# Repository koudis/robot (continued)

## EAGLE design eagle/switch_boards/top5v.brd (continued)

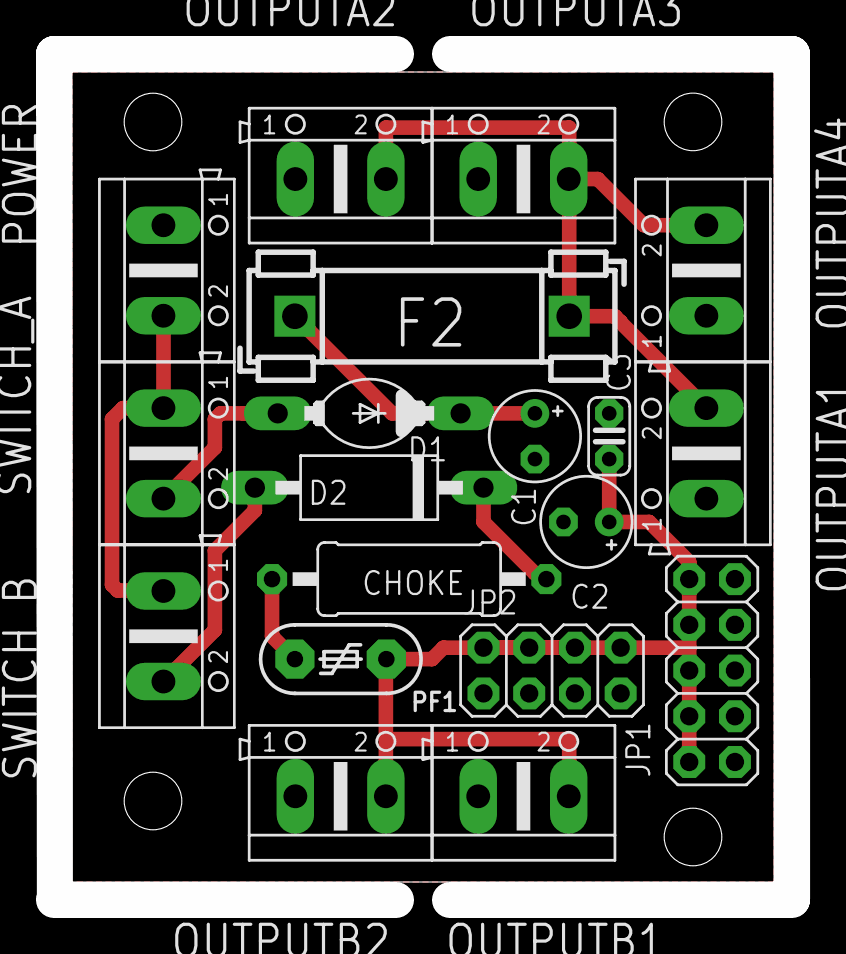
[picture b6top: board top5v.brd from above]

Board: 2 copper layers, 41.0 x 47.0 mm, 19 parts (0 on the bottom side), 9 nets.

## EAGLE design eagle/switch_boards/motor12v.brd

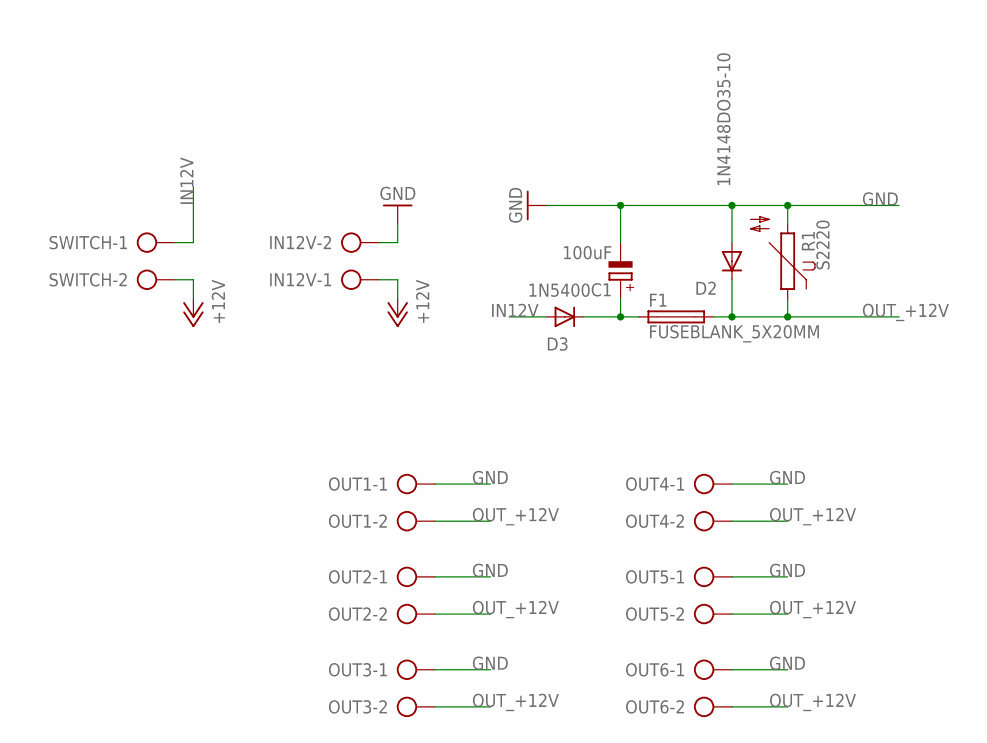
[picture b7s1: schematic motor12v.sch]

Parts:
C1: 100uF; E3,5-8
D2: 1N4148DO35-10; DO35-10
D3: 1N5400; DO201-15
F1: FUSEBLANK_5X20MM; FUSE_HOLDER_5X20MM
IN12V: AK500/2
OUT1, OUT2, OUT3, OUT4, OUT5, OUT6: AK500/2
R1: S2220
SWITCH: AK500/2

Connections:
+12V: IN12V.1, SWITCH.2
EN21: C1.+, D3.C, F1.1
GND: C1.-, D2.A, IN12V.2, OUT1.1, OUT2.1, OUT3.1, OUT4.1, OUT5.1, OUT6.1, R1.2
IN12V: D3.A, SWITCH.1
OUT_+12V: D2.C, F1.2, OUT1.2, OUT2.2, OUT3.2, OUT4.2, OUT5.2, OUT6.2, R1.1

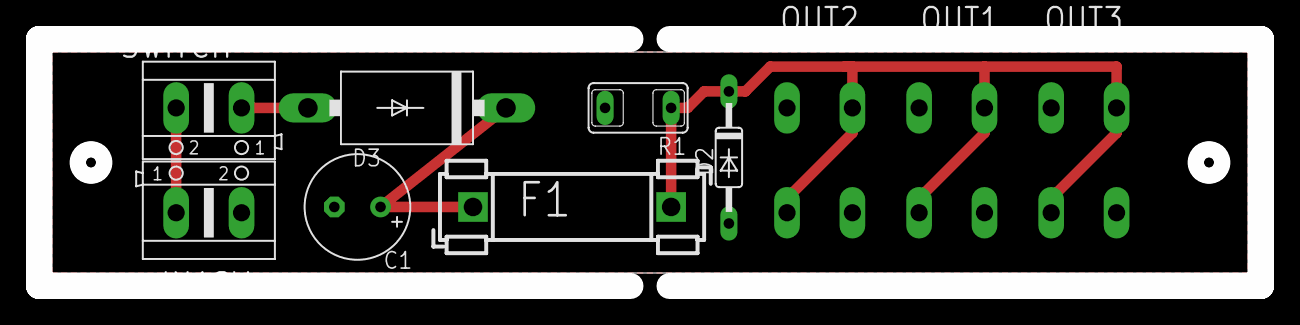
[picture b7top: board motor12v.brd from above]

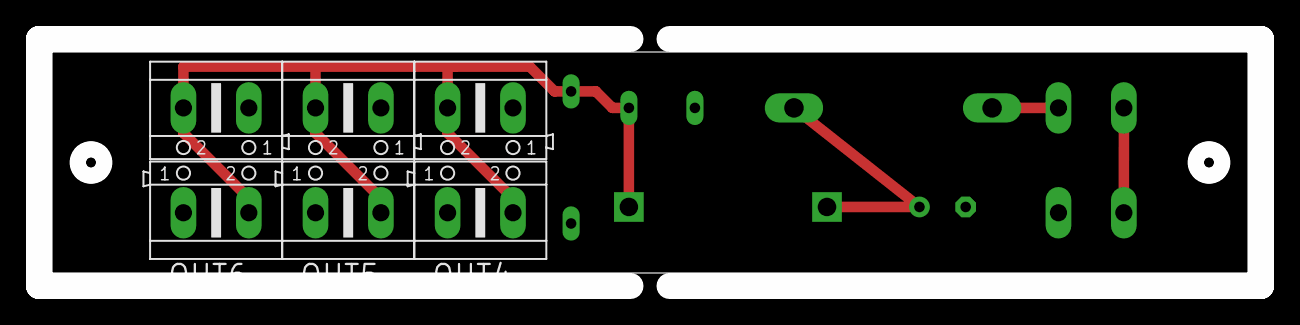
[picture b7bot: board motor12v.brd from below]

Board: 2 copper layers, 94.0 x 19.0 mm, 13 parts (6 on the bottom side), 5 nets.

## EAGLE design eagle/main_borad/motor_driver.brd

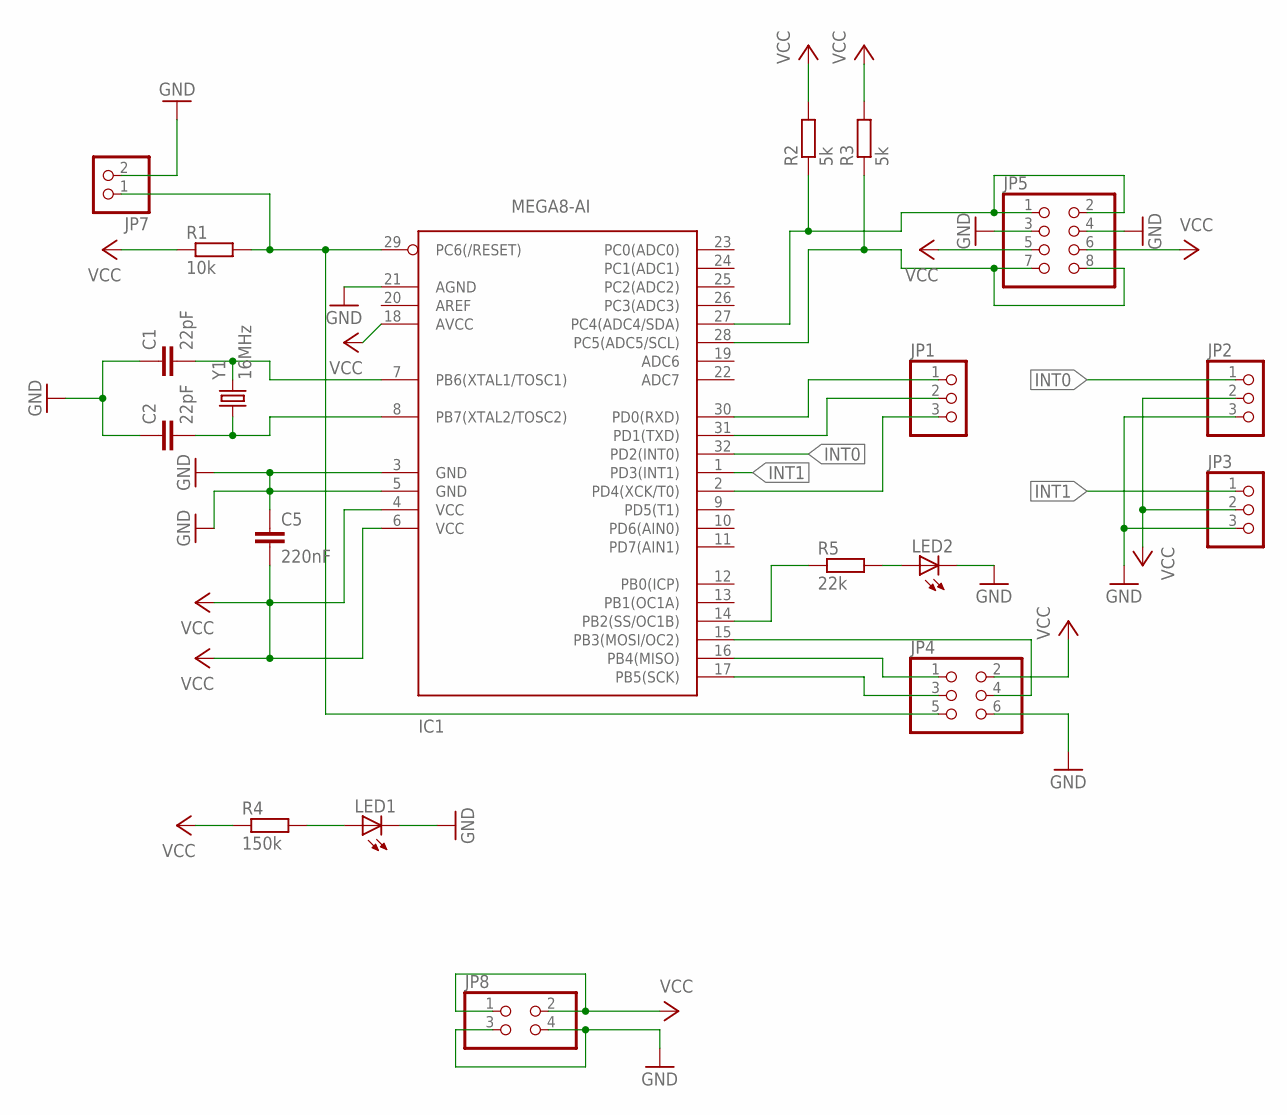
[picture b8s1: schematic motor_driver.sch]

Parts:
C1, C2: 22pF; 1206
C5: 220nF; 0805
IC1: MEGA8-AI; TQFP32-08
JP1, JP2, JP3: PINHD-1X3; 1X03
JP4: PINHD-2X3; 2X03
JP5: PINHD-2X4; 2X04
JP7: PINHD-1X2; 1X02
JP8: PINHD-2X2; 2X02
LED1, LED2: LEDCHIPLED_0805; CHIPLED_0805
R1: 10k; R1206
R2, R3: 5k; R1206
R4: 150k; R0805
R5: 22k; R0805
Y1: 16MHz; HC49UP

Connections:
GND: C1.1, C2.1, C5.1, IC1.3 (GND), IC1.5 (GND), IC1.21 (AGND), JP2.3, JP3.3, JP4.6, JP5.3, JP5.4, JP7.2, JP8.3, JP8.4, LED1.C, LED2.C
INT0: IC1.32 (PD2(INT0)), JP2.1
INT1: IC1.1 (PD3(INT1)), JP3.1
unnamed: IC1.31 (PD1(TXD)), JP1.2
unnamed: C2.2, IC1.8 (PB7(XTAL2/TOSC2)), Y1.1
unnamed: C1.2, IC1.7 (PB6(XTAL1/TOSC1)), Y1.2
unnamed: IC1.14 (PB2(SS/OC1B)), R5.1
unnamed: IC1.30 (PD0(RXD)), JP1.1
unnamed: IC1.2 (PD4(XCK/T0)), JP1.3
unnamed: IC1.15 (PB3(MOSI/OC2)), JP4.4
unnamed: IC1.28 (PC5(ADC5/SCL)), JP5.7, JP5.8, R3.1
unnamed: IC1.27 (PC4(ADC4/SDA)), JP5.1, JP5.2, R2.1
unnamed: LED1.A, R4.2
unnamed: IC1.17 (PB5(SCK)), JP4.3
unnamed: IC1.16 (PB4(MISO)), JP4.1
unnamed: LED2.A, R5.2
RESET: IC1.29 (PC6(/RESET)), JP4.5, JP7.1, R1.2
VCC: C5.2, IC1.4 (VCC), IC1.6 (VCC), IC1.18 (AVCC), JP2.2, JP3.2, JP4.2, JP5.5, JP5.6, JP8.1, JP8.2, R1.1, R2.2, R3.2, R4.1

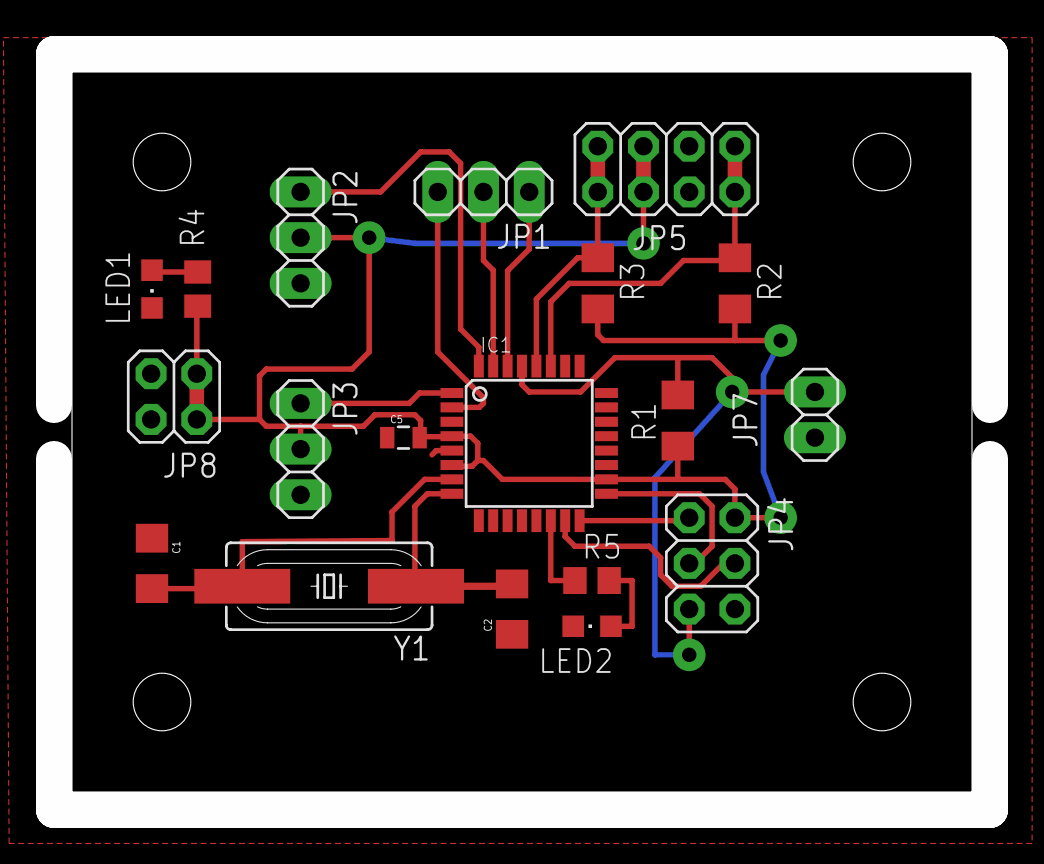
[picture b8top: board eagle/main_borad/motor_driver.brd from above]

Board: 2 copper layers, 52.0 x 42.0 mm, 19 parts (0 on the bottom side), 18 nets.

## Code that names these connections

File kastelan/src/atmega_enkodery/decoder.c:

/*
 *  decoder.c
 *
 *  Created: 2/13/2013 9:58:26 AM
 *  Author: Ondrap, ondrap.cz
 */ 

#define F_CPU 20000000UL  // 20 MHz

#include <avr/io.h>
#include <avr/interrupt.h>
#include <avr/eeprom.h>
#include <util/atomic.h>
#include <util/crc16.h>

#include "TWI_slave.h"
#include "decoder.h"

void writeLedError(uint8_t errorValue){
	PORTB = (PINB & (~7)) | ((errorValue >> 3 ) & 7);
	PORTD = (PIND & ~(7 << 5)) | (errorValue << 5);
}



union doublebyte{
	uint16_t value;
	uint8_t bytes[2];
};

union quadbyte{
	uint32_t value;
	uint8_t bytes[4];
};

struct encoders{
	encval_t left;
	encval_t right;	
};


// decode array for quadrature signal
static uint8_t encoderStateTable[4][2] = {
	{1,2},
	{3,0},
	{0,3},
	{2,1},		
};

uint8_t EEMEM TWI_SlaveAddressEEPROM = DEFAULT_ENCODER_ADDRESS; //set on default address
volatile struct encoders encodersState;

//last quadrature state
uint8_t lastLeftState;
uint8_t lastRightState;
unsigned char messageBuf[TWI_BUFFER_SIZE];

void TWIInit(uint8_t Address){
	// Initialize TWI module for slave operation. Include address and/or enable General Call.
	//TWI_Slave_Initialise( (Address<<TWI_ADR_BITS) | (TRUE<<TWI_GEN_BIT));
	TWI_Slave_Initialise((Address<<TWI_ADR_BITS));
}

// Update I2C address in internal eeprom memory and reinitialize TWI
void setTWIAddress(uint8_t Address){
	if(Address > 127)
		Address = Address >> 1;	// automatic correction if the caller uses the other convention
	
	eeprom_write_byte(&TWI_SlaveAddressEEPROM, Address);
	TWIInit(Address); // reinit the module
}

uint8_t readTWIAddress(){
	return eeprom_read_byte(&TWI_SlaveAddressEEPROM);
}

void setEncodersValue(encval_t l, encval_t r){
	ATOMIC_BLOCK(ATOMIC_RESTORESTATE){
		encodersState.left = l;
		encodersState.right = r;
	}		
}

void setInputInterruptForDecoder(){
	// set interrupt pin as input with pull up 
	PORTC |= (1 << PC1) | (1 << PC0);
	DDRC &= ~((1 << PC1) | (1 << PC0));
	
	PORTD |= (1 << PD1) | (1 << PD0);
	DDRD &= ~((1 << PD1) | (1 << PD0));
	
	// Insert nop for synchronization
	asm volatile ("NOP"::);
	
	// read initial state of decoder
	lastLeftState = PINC & 3;
	lastRightState = PIND & 3;
	
	// enable interrupt 
	PCICR = (1 << PCIE2) | (1 << PCIE1); // use change interrupt PCIE1,2
	PCMSK1 = (1 << PCINT9) | (1 << PCINT8); // enable interrupt on PCINT8,9
	PCMSK2 = (1 << PCINT17) | (1 << PCINT16); // enable interrupt on PCINT16,17
}

void sendEncoders(uint8_t shift){
	union doublebyte L,R; // we always send two-byte value regardless on the internal representation
	ATOMIC_BLOCK(ATOMIC_FORCEON){	
		L.value = encodersState.left >> shift ;
		R.value = encodersState.right >> shift ;
	}
	messageBuf[0] = L.bytes[0];
	messageBuf[1] = L.bytes[1];
	messageBuf[2] = R.bytes[0];
	messageBuf[3] = R.bytes[1];
writeLedError(R.bytes[0]);

	uint8_t crc = 0 , i;
	for(i=0; i<4; ++i){
		crc=_crc_ibutton_update(crc, messageBuf[i]);
	}

	messageBuf[4] = crc;
	
	TWI_Start_Transceiver_With_Data(messageBuf, 5);
}

void sendEncoders32(uint8_t shift){
	union quadbyte L,R; // we always send two-byte value regardless on the internal representation
	ATOMIC_BLOCK(ATOMIC_FORCEON){	
		L.value = encodersState.left >> shift ;
		R.value = encodersState.right >> shift ;
	}
	messageBuf[0] = L.bytes[0];
	messageBuf[1] = L.bytes[1];
	messageBuf[2] = L.bytes[2];
	messageBuf[3] = L.bytes[3];
	messageBuf[4] = R.bytes[0];
	messageBuf[5] = R.bytes[1];
	messageBuf[6] = R.bytes[2];
	messageBuf[7] = R.bytes[3];
writeLedError(R.bytes[0]);

	uint8_t crc = 0 , i;
	for(i=0; i<8; ++i){
		crc=_crc_ibutton_update(crc, messageBuf[i]);
	}

	messageBuf[8] = crc;
	
	TWI_Start_Transceiver_With_Data(messageBuf, 9);
}


ISR(PCINT1_vect, ISR_NOBLOCK){
	uint8_t leftState = PINC & 3;
	
	if(encoderStateTable[lastLeftState][1] == leftState){ // Left wheel had switch second part of array because had opposite direction
		encodersState.left++;
	}else{
		if(encoderStateTable[lastLeftState][0] == leftState){
			encodersState.left--;
		}
		//else{
			// TODO: error 
		//}
	}			
			
	lastLeftState = leftState;
}

ISR(PCINT2_vect, ISR_NOBLOCK){
	uint8_t rightState = PIND & 3;
	
	if(encoderStateTable[lastRightState][0] == rightState){
		encodersState.right++;
	}		
	else{
		if(encoderStateTable[lastRightState][1] == rightState){
			encodersState.right--;
		}
		//else{
			// TODO: error
		//}			
	}			
	
	lastRightState = rightState;
}

int main(void)
{
	setEncodersValue(32767,32767); // a to proc vlastne?
	//setEncodersValue(127,127);

	setEncodersValue(0,0); // a to je vlastne jedno, dam si tam 0.
	
	// set output ports for diodes
	DDRD |= (1 << PD5) | (1 << PD6) | (1 << PD7);
	//PORTD |= (1 << PD5) | (1 << PD6);
	DDRB |= (1 << PB0) | (1 << PB1) | (1 << PB2);
	//PORTB |= (1 << PB0) | (1 << PB1);
	
	writeLedError(0xa);
	setInputInterruptForDecoder();
	
	uint8_t TWI_SlaveAddress;
//	TWI_SlaveAddress = readTWIAddress();
//	if(!TWI_SlaveAddress || TWI_SlaveAddress==0xff)
		TWI_SlaveAddress = DEFAULT_ENCODER_ADDRESS ; // if the EEPROM is not set, we set it to default
	
	TWIInit(TWI_SlaveAddress);
	
	// Enable interrupt
	sei();
	
	// Start the TWI transceiver to enable reception of the first command from the TWI Master.
	TWI_Start_Transceiver();
	
//writeLedError(1);
			
	// Never ending loop witch read from I2C and response on command.
	while(TRUE){
		if(!TWI_Transceiver_Busy()){
			if(TWI_statusReg.RxDataInBuf){
				// get command code
//				writeLedError(2);
				TWI_Get_Data_From_Transceiver(messageBuf, 1);
//				writeLedError(3);
				if((messageBuf[0]&GET_MASK)==GET_ENCODERS){
//					writeLedError(4);
//					PORTD ^=  (1 << PD7);
					sendEncoders(messageBuf[0]&GET_ENCODERS_SHIFT);
				}
				else if((messageBuf[0]&GET_MASK)==GET_ENCODERS_32){
//					writeLedError(5);
//					PORTD ^=  (1 << PD7);
					sendEncoders32(messageBuf[0]&GET_ENCODERS_SHIFT);
				} 
				else switch(messageBuf[0]){
					case SET_ADDRESS:
						{
							uint8_t a;
					writeLedError(6);
							TWI_Get_Data_From_Transceiver((unsigned char*)&a, 1);
							setTWIAddress(a);
						}
					case SET_ENCODERS:
						{
							encval_t l,r;
					writeLedError(7);
							TWI_Get_Data_From_Transceiver((unsigned char*)&l, sizeof(l)); // warning - Endians...
							TWI_Get_Data_From_Transceiver((unsigned char*)&r, sizeof(r));
							setEncodersValue(l,r);
						}	
						break;
					case RESET_ENCODERS:
					writeLedError(8);

						setEncodersValue(0,0);
						break;
					default:
						//writeLedError(5);
						//TWI_Start_Transceiver();
						break;
				}	
			}							
		}
		
		asm volatile ("NOP"::);  // Do something else while waiting			
	}
}

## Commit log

2014-11-23 Init commit
2014-11-23 Structure changes...
2014-11-23 mainborad shema - first version
2014-11-27 Pridany kody pro kastelana
2014-11-27 Added encoders PCB
2014-11-28 New shema for main board
2014-11-28 Added datashets for Atmega8 and XMEGA128A4
2014-12-01 Druha verze navrhu desek pro rizeni podvozku.
2014-12-01 bugfix
2014-12-05 Added .gitignore
2014-12-05 main_board PCB
2014-12-05 main_board PCB ver. 2.0
2014-12-05 motir_driver PCB
2014-12-05 main_board, ver 3.0
2014-12-05 PCB ver. 4.0
2014-12-09 PCB layout 6.0
2014-12-18 Bugs
2015-01-09 Added Makefile for atxmega128a4u
2015-01-09 atxmega128a4uwq
2015-01-21 motor_drivers updated
2015-01-22 robot_driver updated
2015-01-22 otor_driver - led resistors updated
2015-02-01 Atmel twi library for xmega devices
2015-02-08 Added atmega8a datasheet
2015-02-09 NExt version motor_driver
2015-02-09 Repaired motor_driver PCB
2015-02-10 Encoder now works fine :).
2015-02-13 New build macros
2015-02-13 Deleted *.swp files
2015-02-15 BUGFIX in conf/main.mk
2015-02-15 include_program_conf now works fine :).
2015-02-15 Added ENCODER_queadrature library...
2015-02-15 Makefile now works with 'include_program_conf'
2015-02-15 main.atmega8a program updated
    Program now use ENCODER_quadrature library...
2015-02-17 Makefile - BUGFIX
2015-02-23 Makefile - added fuses programing, lib bugfix
2015-02-23 BUGFIX in main.mk
2015-02-23 atmega8a.mk - added MCU_CLASS
2015-02-23 Added config file for main programs
2015-02-23 Reorganizetion lib/ structoru
2015-02-23 Base of comminication protocol...
2015-02-23 Added conf. file for atxmega128a4u (PDI - avr_dragon)
2015-02-23 Huliiduliii :)....
2015-02-23 deleted old xmega_twi library
2015-02-23 xboot added
2015-02-23 Added bootloader for mega devices
2015-02-23 Added readme file with xboot source
2015-02-24 Expansion board v2
2015-02-25 Enable PWN on atmega8a
2015-03-02 Stack....
2015-03-04 Added switchboard for 12v branch
2015-03-04 Added switch board for 5v branch
2015-03-04 atxmega bugfix
2015-03-05 Motor switch board ver. 2.0
2015-03-06 switch board for 5v
2015-03-13 Added function declaration...
2015-03-13 Adeed function pwm_disable
2015-03-13 main.atmega8a - added "prescaller"
2015-03-14 AS5040 encoder datasheets added
2015-03-22 omni chasis simul. script added
2015-03-24 First working version 'omniwheel' firmware
2015-03-25 omni.py - second version
2015-04-12 Changes in command handling, bugfix
2015-04-12 Command system works, bugfixes
2015-04-12 Makefile - gnu99 --> gnu11, -O3 --> -O2
2015-04-12 Omniwheel chasis "simulation"
2015-04-13 env config. available for user...
2015-04-13 FUSES target added to .PHONY
2015-04-13 Forgot piece of code for 'user config'
2015-04-13 TYPO
2015-05-05 Added directory with documentation to smile/doc
2015-05-05 Rename README to README.md
2015-05-05 Doc readme file updated to github markdown language
2015-05-12 All eagle files for smile robot moved to smile/hardware directory -> all source coden and board schematics for smile are now together
2015-07-22 Buxfix in dir structure
2015-10-19 New version "Motor driver"
2015-10-19 hardware/prep.sh script added
2015-11-23 atxmega128a4u prg. options updated
2015-12-07 Added model files for openscad. to view robot model, open robot.scad and F5.
2015-12-08 Added new model files.
2015-12-08 Created model for switchboard 12V.
2016-03-25 save i2c_to_rs485
2016-03-27 i2c to RS485 updated
2016-06-28 i2c to rs485 - testing version
